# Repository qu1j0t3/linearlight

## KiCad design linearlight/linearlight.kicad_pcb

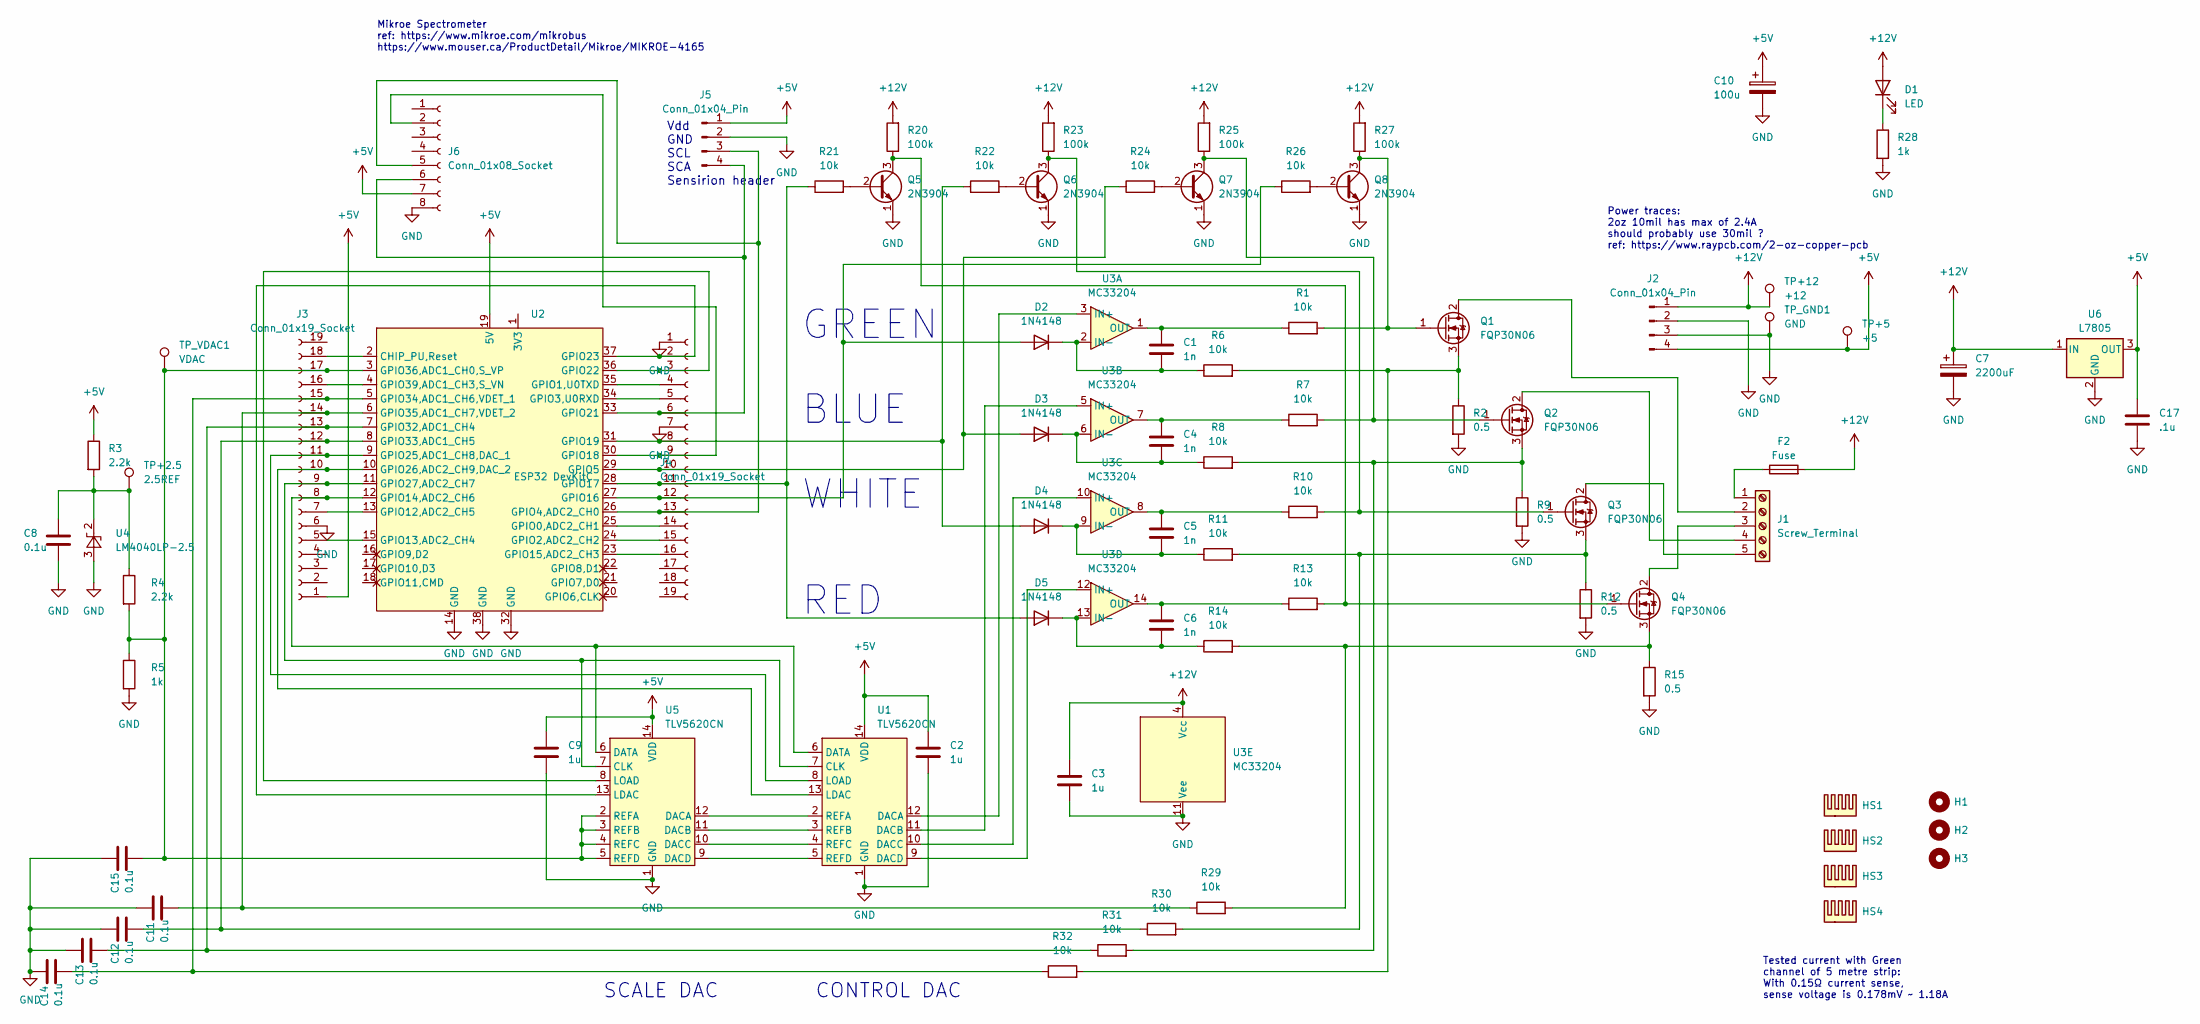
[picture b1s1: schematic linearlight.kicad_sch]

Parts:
C1, C4, C5, C6: 1n; C_Disc_D5.0mm_W2.5mm_P2.50mm
C2, C3, C9: 1u; C_Disc_D5.0mm_W2.5mm_P2.50mm
C7: 2200uF; CP_Radial_D13.0mm_P5.00mm
C8, C11, C12, C13, C14, C15: 0.1u; C_Disc_D5.0mm_W2.5mm_P2.50mm
C10: 100u; CP_Radial_D6.3mm_P2.50mm
C17: .1u; C_Disc_D5.0mm_W2.5mm_P2.50mm
D1: LED; LED_D3.0mm
D2, D3, D4, D5: 1N4148; D_DO-35_SOD27_P7.62mm_Horizontal
F2: Fuse; 01530008
H1, H2, H3: MountingHole_3.2mm_M3
HS1, HS2, HS3, HS4: Max47 heatsink
J1: Screw_Terminal; CONN5_WR-TBL-1377_WRE
J2: Conn_01x04_Pin; 641737-1_TYC
J3, J4: Conn_01x19_Socket; PinSocket_1x19_P2.54mm_Vertical
J5: Conn_01x04_Pin; PinSocket_1x04_P2.54mm_Vertical
J6: Conn_01x08_Socket; PinSocket_1x08_P2.54mm_Vertical
Q1, Q2, Q3, Q4: FQP30N06; TO-220-3_Vertical
Q5, Q6, Q7, Q8: 2N3904; TO-92_Inline_Wide
R1, R6, R7, R8, R10, R11, R13, R14, R21, R22, R24, R26, R29, R30, R31, R32: 10k; R_Axial_DIN0204_L3.6mm_D1.6mm_P7.62mm_Horizontal
R2, R9, R12, R15: 0.5; R_Axial_DIN0414_L11.9mm_D4.5mm_P5.08mm_Vertical
R3, R4: 2.2k; R_Axial_DIN0204_L3.6mm_D1.6mm_P7.62mm_Horizontal
R5: 1k; R_Axial_DIN0207_L6.3mm_D2.5mm_P10.16mm_Horizontal
R20, R23, R25, R27: 100k; R_Axial_DIN0204_L3.6mm_D1.6mm_P7.62mm_Horizontal
R28: 1k; R_Axial_DIN0204_L3.6mm_D1.6mm_P7.62mm_Horizontal
TP+2.5: 2.5REF; TestPoint_THTPad_2.5x2.5mm_Drill1.2mm
TP+5: +5; TestPoint_THTPad_2.5x2.5mm_Drill1.2mm
TP+12: +12; TestPoint_THTPad_2.5x2.5mm_Drill1.2mm
TP_GND1: GND; TestPoint_THTPad_2.5x2.5mm_Drill1.2mm
TP_VDAC1: VDAC; TestPoint_THTPad_2.5x2.5mm_Drill1.2mm
U1, U5: TLV5620CN; DIP-14_W7.62mm_Socket
U2: ESP32 DevKitC; ESP32-DevKitC
U3: MC33204; DIP-14_W7.62mm_Socket
U4: LM4040LP-2.5; TO-92_Inline_Wide
U6: L7805; TO-220-3_Vertical

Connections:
+5V: C2.1, C9.1, C10.1, C17.1, J2.4, J3.1, J5.1, J6.7, R3.1, TP+5.1, U1.14 (VDD), U2.19 (5V), U5.14 (VDD), U6.3 (OUT)
+12V: C3.1, C7.1, D1.2 (A), F2.2, J2.1, R20.2, R23.2, R25.2, R27.2, TP+12.1, U3.4 (Vcc), U6.1 (IN)
GND: C2.2, C3.2, C7.2, C8.2, C9.2, C10.2, C11.1, C12.1, C13.1, C14.1, C15.1, C17.2, J2.2, J2.3, J3.6, J4.1, J4.7, J5.2, J6.8, Q5.1 (E), Q6.1 (E), Q7.1 (E), Q8.1 (E), R2.2, R5.2, R9.2, R12.2, R15.2, R28.2, TP_GND1.1, U1.1 (GND), U2.14 (GND), U2.32 (GND), U2.38 (GND), U3.11 (Vee), U4.3 (A), U5.1 (GND), U6.2 (GND)
unnamed: D1.1 (K), R28.1
unnamed: D2.2 (A), J4.12, R26.1, U2.27 (GPIO16)
unnamed: C1.2, D2.1 (K), R6.1, U3.2 (IN-)
unnamed: D3.2 (A), J4.10, R24.1, U2.29 (GPIO5)
unnamed: C4.2, D3.1 (K), R8.1, U3.6 (IN-)
unnamed: D4.2 (A), J4.8, R22.1, U2.31 (GPIO19)
unnamed: C5.2, D4.1 (K), R11.1, U3.9 (IN-)
unnamed: D5.2 (A), J4.11, R21.1, U2.28 (GPIO17)
unnamed: C6.2, D5.1 (K), R14.1, U3.13 (IN-)
unnamed: F2.1, J1.1
unnamed: J1.2, Q1.2 (D)
unnamed: J1.3, Q4.2 (D)
unnamed: J1.4, Q2.2 (D)
unnamed: J1.5, Q3.2 (D)
unnamed: J3.5, U2.15 (GPIO13,ADC2_CH4)
unnamed: J3.7, U2.13 (GPIO12,ADC2_CH5)
unnamed: J3.8, U1.6 (DATA), U2.12 (GPIO14,ADC2_CH6), U5.6 (DATA)
unnamed: J3.9, U1.7 (CLK), U2.11 (GPIO27,ADC2_CH7), U5.7 (CLK)
unnamed: J3.10, U1.13 (LDAC), U2.10 (GPIO26,ADC2_CH9,DAC_2)
unnamed: J3.11, U1.8 (LOAD), U2.9 (GPIO25,ADC1_CH8,DAC_1)
unnamed: C12.2, J3.12, R30.1, U2.8 (GPIO33,ADC1_CH5)
unnamed: C13.2, J3.13, R31.1, U2.7 (GPIO32,ADC1_CH4)
unnamed: C11.2, J3.14, R29.1, U2.6 (GPIO35,ADC1_CH7,VDET_2)
unnamed: C14.2, J3.15, R32.1, U2.5 (GPIO34,ADC1_CH6,VDET_1)
unnamed: J3.16, U2.4 (GPIO39,ADC1_CH3,S_VN)
unnamed: C15.2, J3.17, R4.2, R5.1, TP_VDAC1.1, U2.3 (GPIO36,ADC1_CH0,S_VP), U5.2 (REFA), U5.3 (REFB), U5.4 (REFC), U5.5 (REFD)
unnamed: J3.18, U2.2 (CHIP_PU,Reset)
unnamed: J4.2, U2.37 (GPIO23), U5.13 (LDAC)
unnamed: J4.3, U2.36 (GPIO22), U5.8 (LOAD)
unnamed: J4.4, U2.35 (GPIO1,U0TXD)
unnamed: J4.5, U2.34 (GPIO3,U0RXD)
unnamed: J4.6, J5.4, J6.6, U2.33 (GPIO21)
unnamed: J4.9, J6.2, U2.30 (GPIO18)
unnamed: J4.13, J5.3, J6.5, U2.26 (GPIO4,ADC2_CH0)
unnamed: J4.14, U2.25 (GPIO0,ADC2_CH1)
unnamed: J4.15, U2.24 (GPIO2,ADC2_CH2)
unnamed: J4.16, U2.23 (GPIO15,ADC2_CH3)
unnamed: Q1.1 (G), Q8.3 (C), R1.2, R27.1
unnamed: Q1.3 (S), R2.1, R6.2, R32.2
unnamed: Q2.1 (G), Q7.3 (C), R7.2, R25.1
unnamed: Q2.3 (S), R8.2, R9.1, R31.2
unnamed: Q3.1 (G), Q6.3 (C), R10.2, R23.1
unnamed: Q3.3 (S), R11.2, R12.1, R30.2
unnamed: Q4.1 (G), Q5.3 (C), R13.2, R20.1
unnamed: Q4.3 (S), R14.2, R15.1, R29.2
unnamed: Q5.2 (B), R21.2
unnamed: Q6.2 (B), R22.2
unnamed: Q7.2 (B), R24.2
unnamed: Q8.2 (B), R26.2
unnamed: U1.12 (DACA), U3.3 (IN+)
unnamed: U1.11 (DACB), U3.5 (IN+)
unnamed: U1.10 (DACC), U3.10 (IN+)
unnamed: U1.9 (DACD), U3.12 (IN+)
unnamed: U1.2 (REFA), U5.12 (DACA)
unnamed: U1.3 (REFB), U5.11 (DACB)
unnamed: U1.4 (REFC), U5.10 (DACC)
unnamed: U1.5 (REFD), U5.9 (DACD)
unnamed: C1.1, R1.1, U3.1 (OUT)
unnamed: C4.1, R7.1, U3.7 (OUT)
unnamed: C5.1, R10.1, U3.8 (OUT)
unnamed: C6.1, R13.1, U3.14 (OUT)
unnamed: C8.1, R3.2, R4.1, TP+2.5.1, U4.2 (K)

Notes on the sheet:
Tested current with Green channel of 5 metre strip: With 0.15Ω current sense, sense voltage is 0.178mV ~ 1.18A
WHITE
SCALE DAC
BLUE
CONTROL DAC
GREEN
Vdd GND SCL SCA Sensirion header
RED
Mikroe Spectrometer ref: https://www.mikroe.com/mikrobus https://www.mouser.ca/ProductDetail/Mikroe/MIKROE-4165
Power traces: 2oz 10mil has max of 2.4A should probably use 30mil ? ref: https://www.raypcb.com/2-oz-copper-pcb

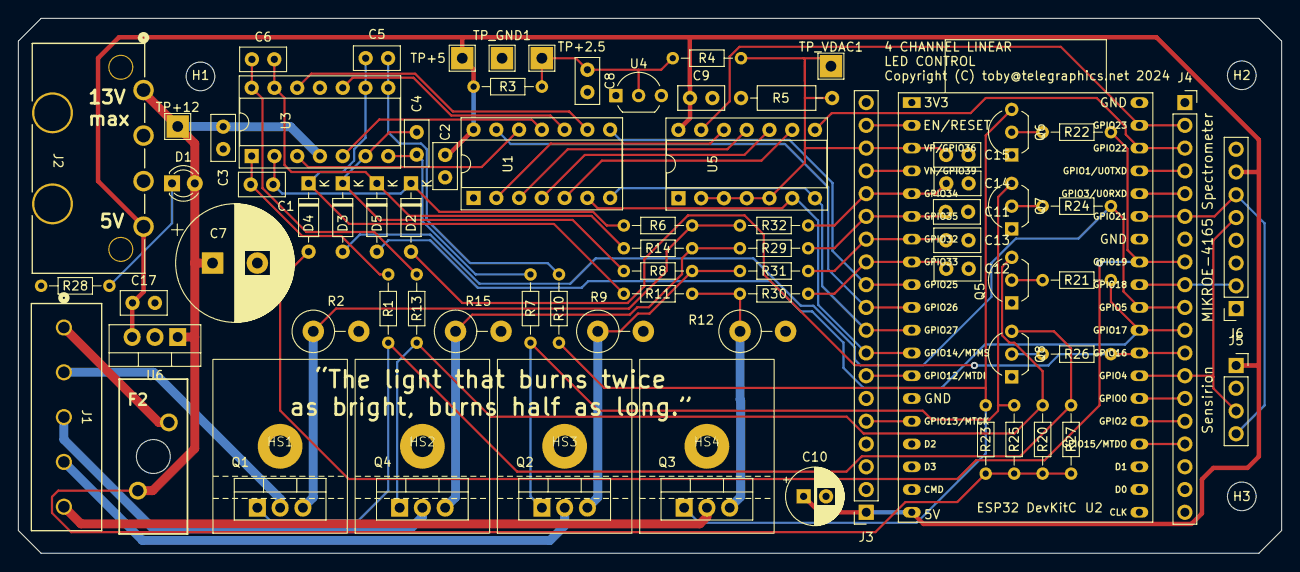
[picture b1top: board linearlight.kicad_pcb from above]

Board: 2 copper layers, 141.0 x 59.7 mm, 82 parts (0 on the bottom side), 65 nets.

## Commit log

2024-01-21 Initial commit.
2024-01-25 Updates including 2nd DAC for nonlinear response.
2024-02-11 PCB layout passes DRC.
2024-02-11 Release candidate 1
2024-02-11 Release candidate 2
2024-02-11 Add cnx for spectrometer.
2024-02-18 Release candidate 3
2024-02-19 Production 2024-02-18
2024-05-22 Add API exerciser and calibrator.
2024-05-22 Add usage text

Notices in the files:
linearlight/linearlight.kicad_pcb:
Copyright (C) toby@telegraphics.net 2024
